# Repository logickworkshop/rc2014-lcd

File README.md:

# RC2014 16x2 LCD Display Module

## The Module

The schematic for this module is based on an excellent blog post about
[connecting an LCD to a Z80 with two glue chips][1] by Mike Sutton (or more
accurately, on my own attempt to do the same thing, reaching nearly the same
design, then finding Mike's blog post and adopting his design wholesale). One
of eight I/O ports can be selected using a jumper, and the command and
character modes use two adjacent addresses.

The PCB provides a 16-pin header compatible with standard 16x2 LCD modules,
and should fit many of them within the footprint of the board if the headers
are soldered at the top of the module.

Note that at the nominal 7.3728Mhz clock speed of the RC2014, the enable
signal will only be held for about 68ns. Check the timing diagram in your LCD
display module's datasheet to ensure compatibility.

### Bill of Materials

* 74HCT138N (PDIP16)
* 74HCT04N (PDIP14)
* 2 x 0.1uF ceramic capacitor (radial, 5mm lead spacing)
* 10K linear trim potentiometer (single turn, B25P footprint)
* 39-pin single right-angle 0.1" header
* 16-pin double straight 0.1" header
* 16-pin single straight 0.1" header
* 16-pin DIP socket (optional)
* 14-pin DIP socket (optional)

## The Code

The example program `LCD.ZSM` is designed to work on CP/M, and can be built
using [ZSM][2]. Note that the I/O port addresses are hard-coded, and will need
to be changed to reflect your jumper setting.

[1]: https://bread80.com/2020/07/01/connecting-an-lcd-to-a-z80-with-two-glue-chips/
[2]: https://github.com/MiguelVis/zsm

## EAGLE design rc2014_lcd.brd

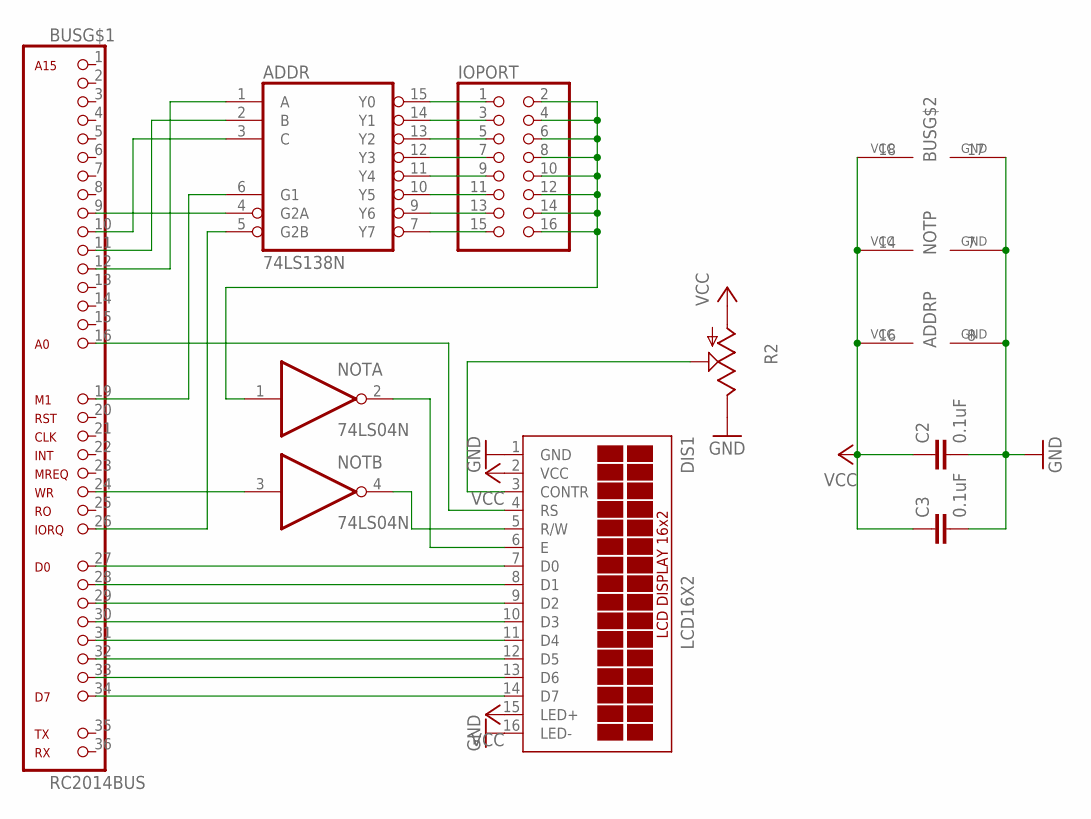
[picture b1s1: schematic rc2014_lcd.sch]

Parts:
ADDR: 74LS138N; DIL16
BUS: RC2014BUS; 1X39
C2, C3: 0.1uF; C050-024X044
DIS1: LCD16X2; 1X16
IOPORT: PINHD-2X8; 2X08
NOT: 74LS04N; DIL14
R2: TRIM_US-B25P; B25P

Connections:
GND: ADDR.8 (GND), BUS.17 (GND), C2.2, C3.2, DIS1.1 (GND), DIS1.16 (LED-), NOT.7 (GND), R2.E
unnamed: ADDR.6 (G1), BUS.19 (M1)
unnamed: ADDR.5 (G2B), BUS.26 (IORQ)
unnamed: ADDR.4 (G2A), BUS.9 (A7)
unnamed: ADDR.3 (C), BUS.10 (A6)
unnamed: ADDR.2 (B), BUS.11 (A5)
unnamed: ADDR.1 (A), BUS.12 (A4)
unnamed: ADDR.15 (Y0), IOPORT.1
unnamed: ADDR.14 (Y1), IOPORT.3
unnamed: ADDR.13 (Y2), IOPORT.5
unnamed: ADDR.12 (Y3), IOPORT.7
unnamed: ADDR.11 (Y4), IOPORT.9
unnamed: ADDR.10 (Y5), IOPORT.11
unnamed: ADDR.9 (Y6), IOPORT.13
unnamed: ADDR.7 (Y7), IOPORT.15
unnamed: IOPORT.2, IOPORT.4, IOPORT.6, IOPORT.8, IOPORT.10, IOPORT.12, IOPORT.14, IOPORT.16, NOT.1 (I)
unnamed: BUS.27 (D0), DIS1.7 (D0)
unnamed: BUS.28 (D1), DIS1.8 (D1)
unnamed: BUS.29 (D2), DIS1.9 (D2)
unnamed: BUS.30 (D3), DIS1.10 (D3)
unnamed: BUS.31 (D4), DIS1.11 (D4)
unnamed: BUS.32 (D5), DIS1.12 (D5)
unnamed: BUS.33 (D6), DIS1.13 (D6)
unnamed: BUS.34 (D7), DIS1.14 (D7)
unnamed: BUS.24 (WR), NOT.3 (I)
unnamed: DIS1.5 (R/W), NOT.4 (O)
unnamed: BUS.16 (A0), DIS1.4 (RS)
unnamed: DIS1.6 (E), NOT.2 (O)
unnamed: DIS1.3 (CONTR), R2.S
VCC: ADDR.16 (VCC), BUS.18 (VCC), C2.1, C3.1, DIS1.2 (VCC), DIS1.15 (LED+), NOT.14 (VCC), R2.A

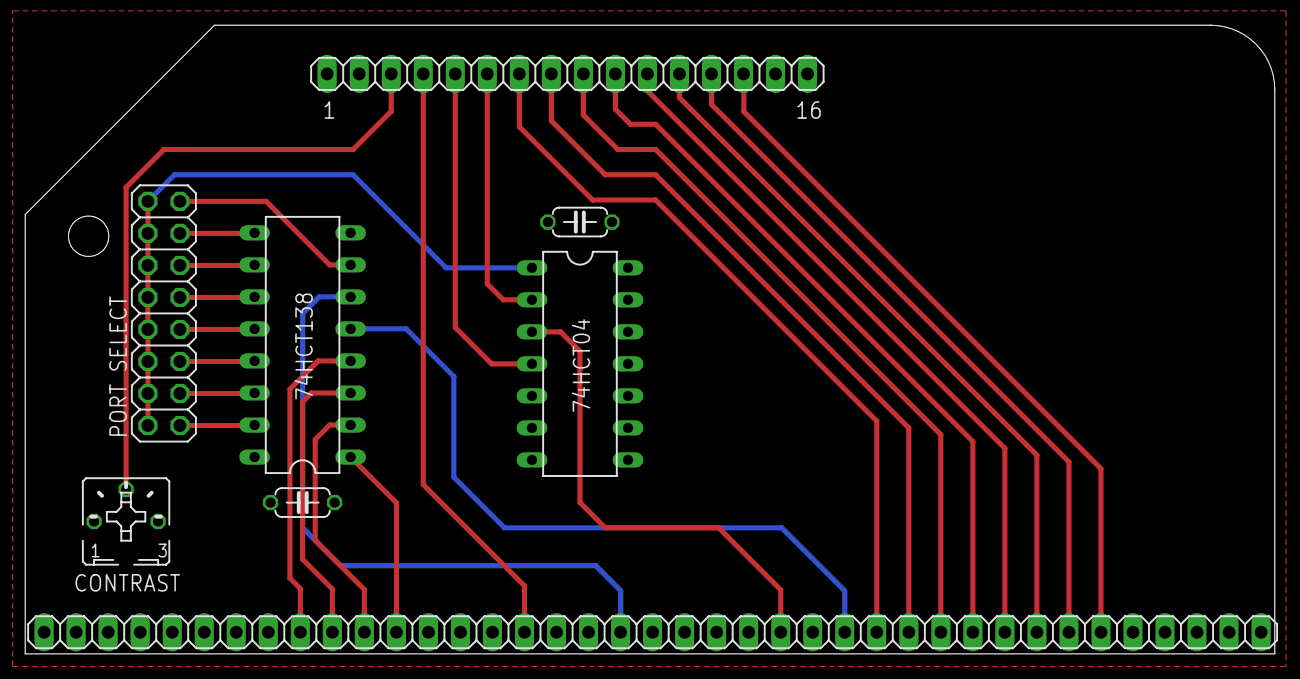
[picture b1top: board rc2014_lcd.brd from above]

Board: 2 copper layers, 99.1 x 49.9 mm, 8 parts (0 on the bottom side), 30 nets.

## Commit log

2022-09-16 Add schematic and board design.
2022-09-16 Add example control program in Z80 assembly.
2022-09-16 Populate README.
2022-09-16 Add note about hard-coded addresses.
2022-09-16 Add BOM to README.
2022-09-16 Correct axial to radial.
2022-09-16 Specify trim potentiometer specs.
